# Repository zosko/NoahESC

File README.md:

# NoahESC
The Atmega8-based Electronic Speed Controller (ESC) is a motor control device that uses the Atmega8 microcontroller as its main processing unit. It is designed to regulate the speed, direction, and braking of brushless DC (BLDC) motors or brushed motors, depending on the application. The Atmega8 handles the input signals—typically from a flight controller or receiver—and converts them into precise pulse-width modulation (PWM) outputs to control the motor’s performance. This type of ESC is widely used in drones, RC vehicles, and robotics projects due to its reliability, programmability, and compatibility with open-source firmware such as TGY. Overall, it provides an efficient and flexible solution for motor speed control in embedded and hobbyist applications.

### Features
- [X] PWM
- [X] 30Amps
- [X] 2 - 4S battery
- [X] Low cost

## Scheme

## Boards Preview
Board|PCB
---------|---------
|

### Flashing
Atmega8 must be flashed via ICSP microcontroller pins. 

**Arduino UNO as ISP programmer**
- `avrdude -c stk500v1 -p m8 -P /dev/tty.usbmodem14401 -b 19200 -U flash:w:firmware.hex:i`
- `avrdude -c stk500v1 -p m8 -P /dev/tty.usbmodem14401 -b 19200 -U lfuse:w:0x3f:m -U hfuse:w:0xca:m`

**USBasp**
- `avrdude -c usbasp -p m8 -U flash:w:firmware.hex:i`
- `avrdude -c usbasp -p m8 -U lfuse:w:0x3f:m -U hfuse:w:0xca:m`

**Download**: [Firmware](firmware.hex)

## PCB Design

**Huge thanks to [PCBWay](https://pcbway.com) for sponsoring this project!**

PCBWay is a leading provider of high-quality printed circuit boards (PCBs), offering reliable and affordable solutions for both hobbyists and professionals. Their services include rapid prototyping, PCB assembly, instant online quotations, expert design verification, and a streamlined ordering experience.

Their comprehensive range of services includes:
- PCB prototyping
- Assembly services
- Instant online quotations
- Expert design verification
- A streamlined, user-friendly ordering system

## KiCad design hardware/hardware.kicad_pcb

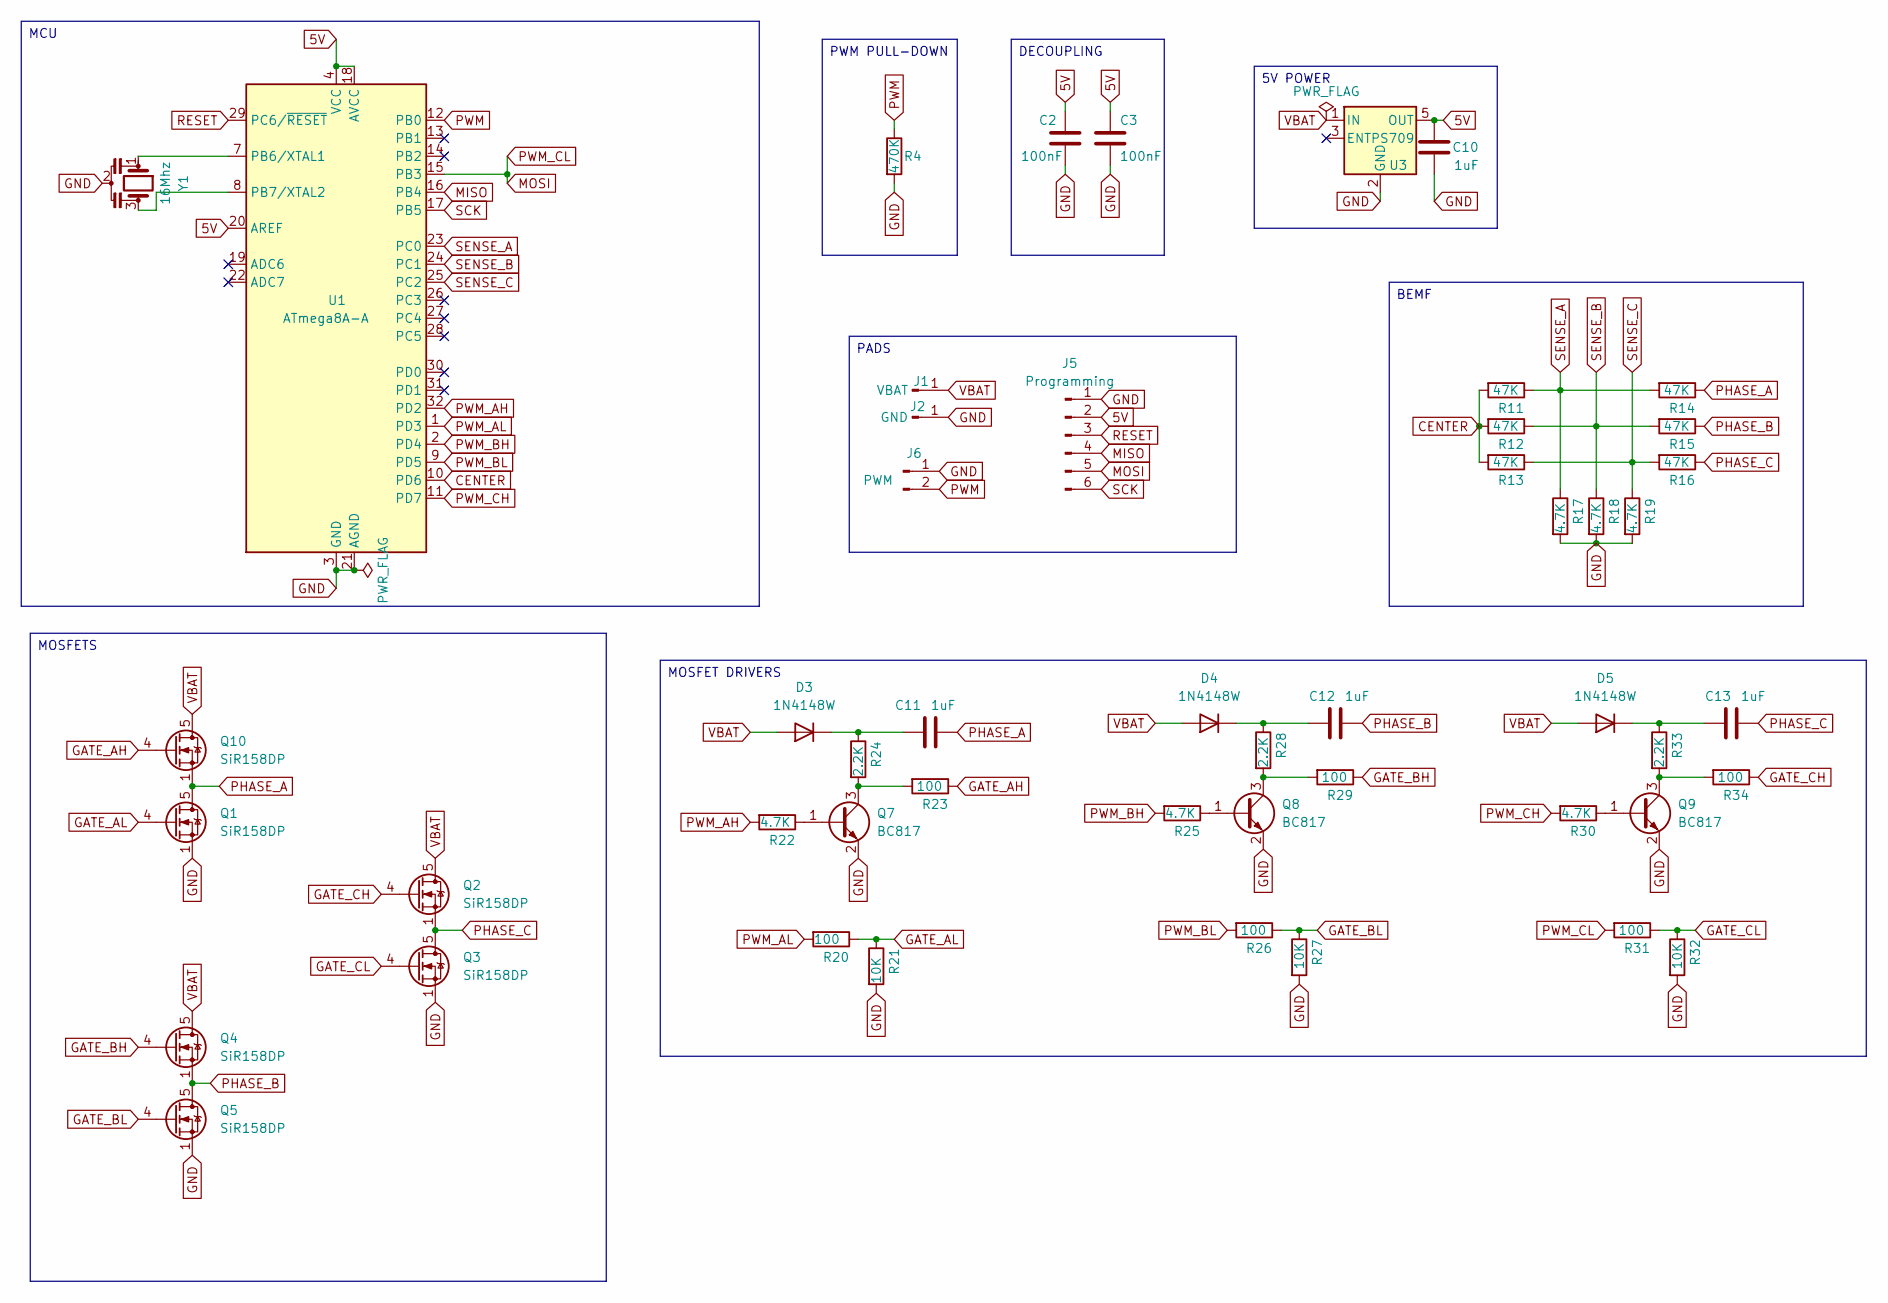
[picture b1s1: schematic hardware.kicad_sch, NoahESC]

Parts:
C2, C3: 100nF; C_0805_2012Metric_Pad1.18x1.45mm_HandSolder; LCSC C49678
C10, C11, C12, C13: 1uF; C_0805_2012Metric_Pad1.18x1.45mm_HandSolder; LCSC C28323
D3, D4, D5: 1N4148W; D_SOD-123; LCSC C241939
J1: VBAT; TestPoint_Pad_3.0x3.0mm
J2: GND; TestPoint_Pad_3.0x3.0mm
J5: Programming; PinHeader_1x06_P1.27mm_Vertical; LCSC C22438289
J6: PWM; PinHeader_1x02_P2.54mm_Vertical; LCSC C42431798
Q1, Q2, Q3, Q4, Q5, Q10: SiR158DP; PowerPAK_SO-8_Single; LCSC C142530
Q7, Q8, Q9: BC817; SOT-23; LCSC C39828
R4: 470K; R_0805_2012Metric_Pad1.20x1.40mm_HandSolder; LCSC C89104
R11, R12, R13, R14, R15, R16: 47K; R_0805_2012Metric_Pad1.20x1.40mm_HandSolder; LCSC C17713
R17, R18, R19, R22, R25, R30: 4.7K; R_0805_2012Metric_Pad1.20x1.40mm_HandSolder; LCSC C17673
R20, R23, R26, R29, R31, R34: 100; R_0805_2012Metric_Pad1.20x1.40mm_HandSolder; LCSC C17408
R21, R27, R32: 10K; R_0805_2012Metric_Pad1.20x1.40mm_HandSolder; LCSC C84376
R24, R28, R33: 2.2K; R_0805_2012Metric_Pad1.20x1.40mm_HandSolder; LCSC C17520
U1: ATmega8A-A; TQFP-32_7x7mm_P0.8mm; LCSC C16190
U3: TPS709; SOT-23-5; LCSC C2865456
Y1: 16Mhz; Resonator_SMD_Murata_CSTxExxV-3Pin_3.0x1.1mm; LCSC C882606

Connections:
5V: C2.1, C3.1, C10.2, J5.2, U1.4 (VCC), U1.6 (VCC), U1.18 (AVCC), U1.20 (AREF), U3.5 (OUT)
CENTER: R11.2, R12.2, R13.2, U1.10 (PD6)
GATE_AH: Q10.4 (G), R23.1
GATE_AL: Q1.4 (G), R20.1, R21.1
GATE_BH: Q4.4 (G), R29.1
GATE_BL: Q5.4 (G), R26.1, R27.1
GATE_CH: Q2.4 (G), R34.1
GATE_CL: Q3.4 (G), R31.1, R32.1
GND: C2.2, C3.2, C10.1, J2.1, J5.1, J6.1, Q1.1 (S), Q1.2 (S), Q1.3 (S), Q3.1 (S), Q3.2 (S), Q3.3 (S), Q5.1 (S), Q5.2 (S), Q5.3 (S), Q7.2 (E), Q8.2 (E), Q9.2 (E), R4.2, R17.2, R18.2, R19.2, R21.2, R27.2, R32.2, U1.3 (GND), U1.5 (GND), U1.21 (AGND), U3.2 (GND), Y1.2
MISO: J5.4, U1.16 (PB4)
MOSI: J5.5, R31.2, U1.15 (PB3)
unnamed: C11.2, D3.1 (K), R24.1
unnamed: C12.2, D4.1 (K), R28.1
unnamed: C13.2, D5.1 (K), R33.1
unnamed: Q7.1 (B), R22.1
unnamed: Q7.3 (C), R23.2, R24.2
unnamed: Q8.1 (B), R25.1
unnamed: Q8.3 (C), R28.2, R29.2
unnamed: Q9.1 (B), R30.1
unnamed: Q9.3 (C), R33.2, R34.2
unnamed: U1.7 (PB6/XTAL1), Y1.1
unnamed: U1.8 (PB7/XTAL2), Y1.3
PHASE_A: C11.1, Q1.5 (D), Q10.1 (S), Q10.2 (S), Q10.3 (S), R14.1
PHASE_B: C12.1, Q4.1 (S), Q4.2 (S), Q4.3 (S), Q5.5 (D), R15.1
PHASE_C: C13.1, Q2.1 (S), Q2.2 (S), Q2.3 (S), Q3.5 (D), R16.1
PWM: J6.2, R4.1, U1.12 (PB0)
PWM_AH: R22.2, U1.32 (PD2)
PWM_AL: R20.2, U1.1 (PD3)
PWM_BH: R25.2, U1.2 (PD4)
PWM_BL: R26.2, U1.9 (PD5)
PWM_CH: R30.2, U1.11 (PD7)
RESET: J5.3, U1.29 (PC6/~RESET)
SCK: J5.6, U1.17 (PB5)
SENSE_A: R11.1, R14.2, R17.1, U1.23 (PC0)
SENSE_B: R12.1, R15.2, R18.1, U1.24 (PC1)
SENSE_C: R13.1, R16.2, R19.1, U1.25 (PC2)
VBAT: D3.2 (A), D4.2 (A), D5.2 (A), J1.1, Q2.5 (D), Q4.5 (D), Q10.5 (D), U3.1 (IN)

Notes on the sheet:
MCU
BEMF
5V POWER
PADS
DECOUPLING
MOSFET DRIVERS
PWM PULL-DOWN
MOSFETS

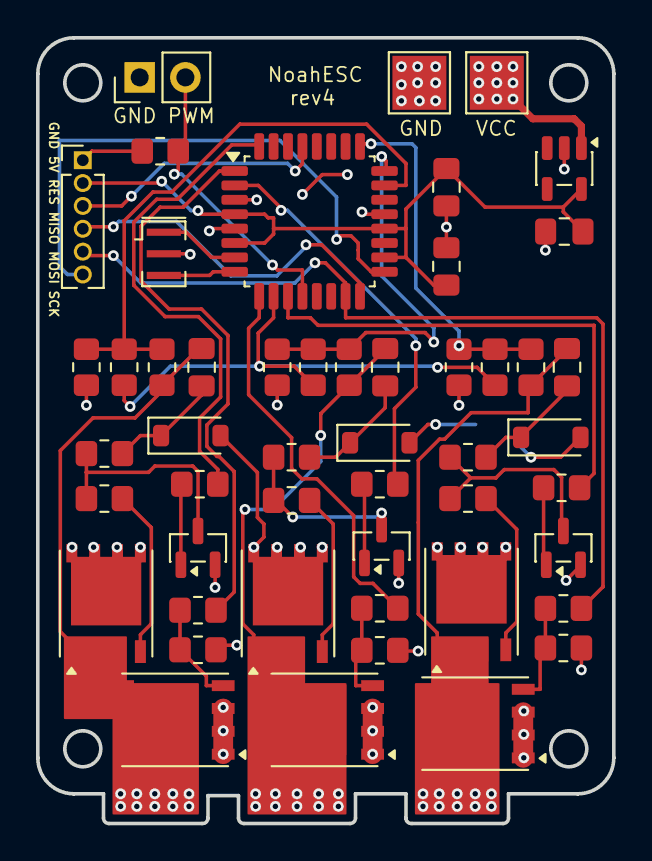
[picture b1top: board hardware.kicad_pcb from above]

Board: 2 copper layers, 32.0 x 43.7 mm, 50 parts (0 on the bottom side), 37 nets.

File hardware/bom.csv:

"Reference","Value","LCSC"
"C2,C3","100nF","C49678"
"C10,C11,C12,C13","1uF","C28323"
"D3,D4,D5","1N4148W","C241939"
"J1","VBAT",""
"J2,J3","GND",""
"J4","PWM",""
"J5","Programming","C22438289"
"Q1,Q2,Q3,Q4,Q5,Q10","SiR158DP","C142530"
"Q7,Q8,Q9","BC817","C39828"
"R4","470K","C89104"
"R11,R12,R13,R14,R15,R16","47K","C17713"
"R17,R18,R19,R22,R25,R30","4.7K","C17673"
"R20,R23,R26,R29,R31,R34","100","C17408"
"R21,R27,R32","10K","C84376"
"R24,R28,R33","2.2K","C17520"
"U1","ATmega8A-A","C16190"
"U3","TPS709","C2865456"
"Y1","16Mhz","C882606"

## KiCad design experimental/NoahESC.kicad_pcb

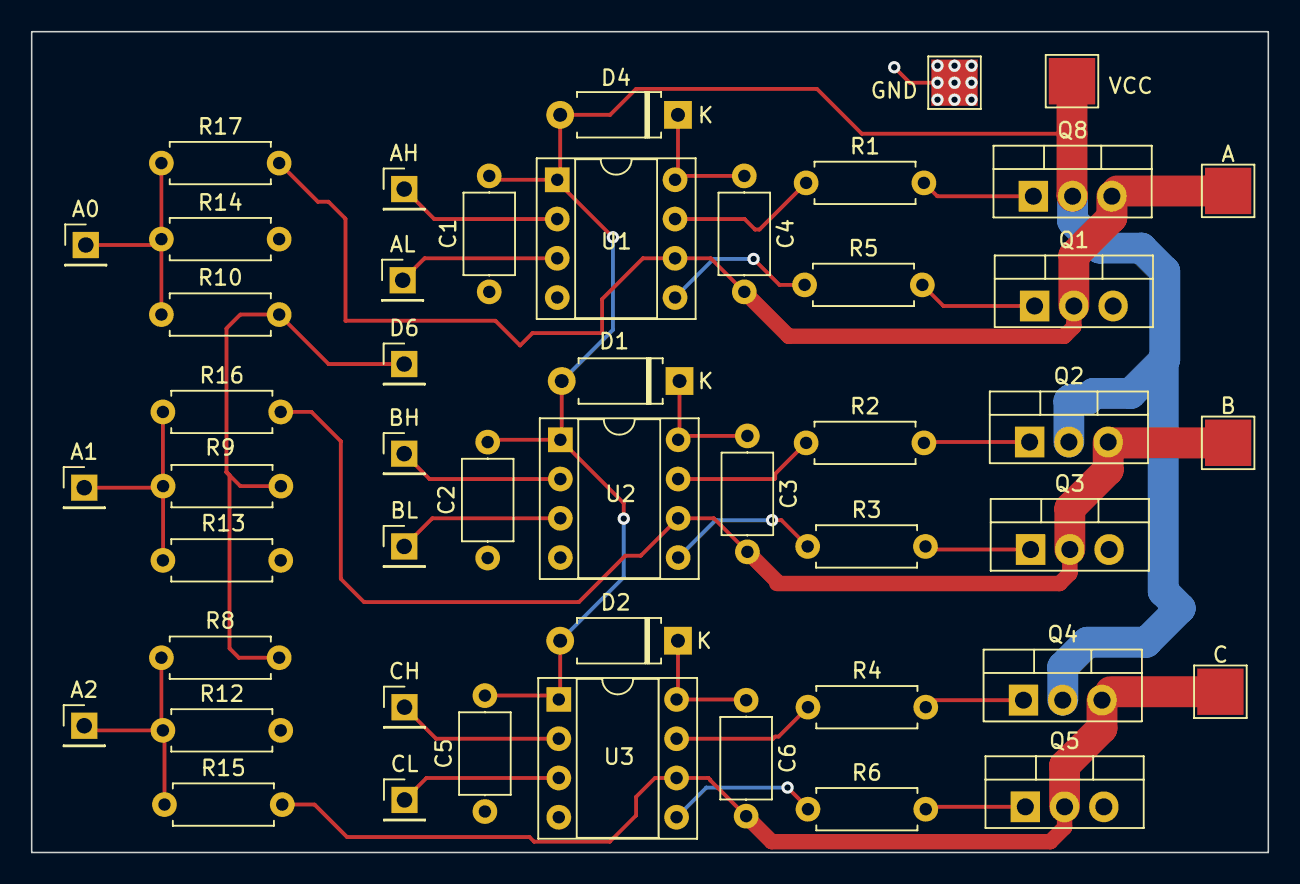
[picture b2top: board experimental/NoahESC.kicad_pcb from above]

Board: 2 copper layers, 80.0 x 53.1 mm, 48 parts (0 on the bottom side), 30 nets.

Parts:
A: PHASE_A; TestPoint_Pad_3.0x3.0mm
A0: A0; PinHeader_1x01_P2.54mm_Vertical
A1: A1; PinHeader_1x01_P2.54mm_Vertical
A2: A2; PinHeader_1x01_P2.54mm_Vertical
AH: AH; PinHeader_1x01_P2.54mm_Vertical
AL: AL; PinHeader_1x01_P2.54mm_Vertical
B: PHASE_B; TestPoint_Pad_3.0x3.0mm
BH: BH; PinHeader_1x01_P2.54mm_Vertical
BL: BL; PinHeader_1x01_P2.54mm_Vertical
C: PHASE_C; TestPoint_Pad_3.0x3.0mm
C1, C2, C5: 10uF; C_Axial_L5.1mm_D3.1mm_P7.50mm_Horizontal
C3, C4, C6: 2.2uF; C_Axial_L5.1mm_D3.1mm_P7.50mm_Horizontal
CH: CH; PinHeader_1x01_P2.54mm_Vertical
CL: CL; PinHeader_1x01_P2.54mm_Vertical
D1, D2, D4: D; D_A-405_P7.62mm_Horizontal
D6: D6; PinHeader_1x01_P2.54mm_Vertical
GND: GND; TestPoint_Pad_3.0x3.0mm
Q1, Q2, Q3, Q4, Q5, Q8: NMOS; TO-220-3_Vertical
R1, R2, R3, R4, R5, R6: 100; R_Axial_DIN0207_L6.3mm_D2.5mm_P7.62mm_Horizontal
R8, R9, R10, R15, R16, R17: 33K; R_Axial_DIN0207_L6.3mm_D2.5mm_P7.62mm_Horizontal
R12, R13, R14: 10K; R_Axial_DIN0207_L6.3mm_D2.5mm_P7.62mm_Horizontal
U1, U2, U3: IR2101; DIP-8_W7.62mm_Socket
VCC: 12V; TestPoint_Pad_3.0x3.0mm

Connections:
12V: C1.2, C2.2, C5.2, D1.2 (A), D2.2 (A), D4.2 (A), Q2.2 (D), Q4.2 (D), Q8.2 (D), U1.1 (VCC), U2.1 (VCC), U3.1 (VCC), VCC.1
A0: A0.1, R10.2, R14.1, R17.1
A1: A1.1, R9.2, R13.1, R16.1
A2: A2.1, R8.2, R12.1, R15.1
AH: AH.1, U1.2 (HIN)
AL: AL.1, U1.3 (LIN)
BH: BH.1, U2.2 (HIN)
BL: BL.1, U2.3 (LIN)
CH: CH.1, U3.2 (HIN)
CL: CL.1, U3.3 (LIN)
D6: D6.1, R8.1, R9.1, R10.1
GND: C1.1, C2.1, C5.1, GND.1, Q1.3 (S), Q3.3 (S), Q5.3 (S), R12.2, R13.2, R14.2, U1.4 (COM), U2.4 (COM), U3.4 (COM)
unnamed: C3.1, D1.1 (K), U2.8 (VB)
unnamed: C6.1, D2.1 (K), U3.8 (VB)
unnamed: C4.1, D4.1 (K), U1.8 (VB)
unnamed: Q1.1 (G), R5.2
unnamed: Q2.1 (G), R2.2
unnamed: Q3.1 (G), R3.2
unnamed: Q4.1 (G), R4.2
unnamed: Q5.1 (G), R6.2
unnamed: Q8.1 (G), R1.2
unnamed: R1.1, U1.7 (HO)
unnamed: R5.1, U1.5 (LO)
unnamed: R2.1, U2.7 (HO)
unnamed: R3.1, U2.5 (LO)
unnamed: R4.1, U3.7 (HO)
unnamed: R6.1, U3.5 (LO)
PHASE_A: A.1, C4.2, Q1.2 (D), Q8.3 (S), R17.2, U1.6 (VS)
PHASE_B: B.1, C3.2, Q2.3 (S), Q3.2 (D), R16.2, U2.6 (VS)
PHASE_C: C.1, C6.2, Q4.3 (S), Q5.2 (D), R15.2, U3.6 (VS)

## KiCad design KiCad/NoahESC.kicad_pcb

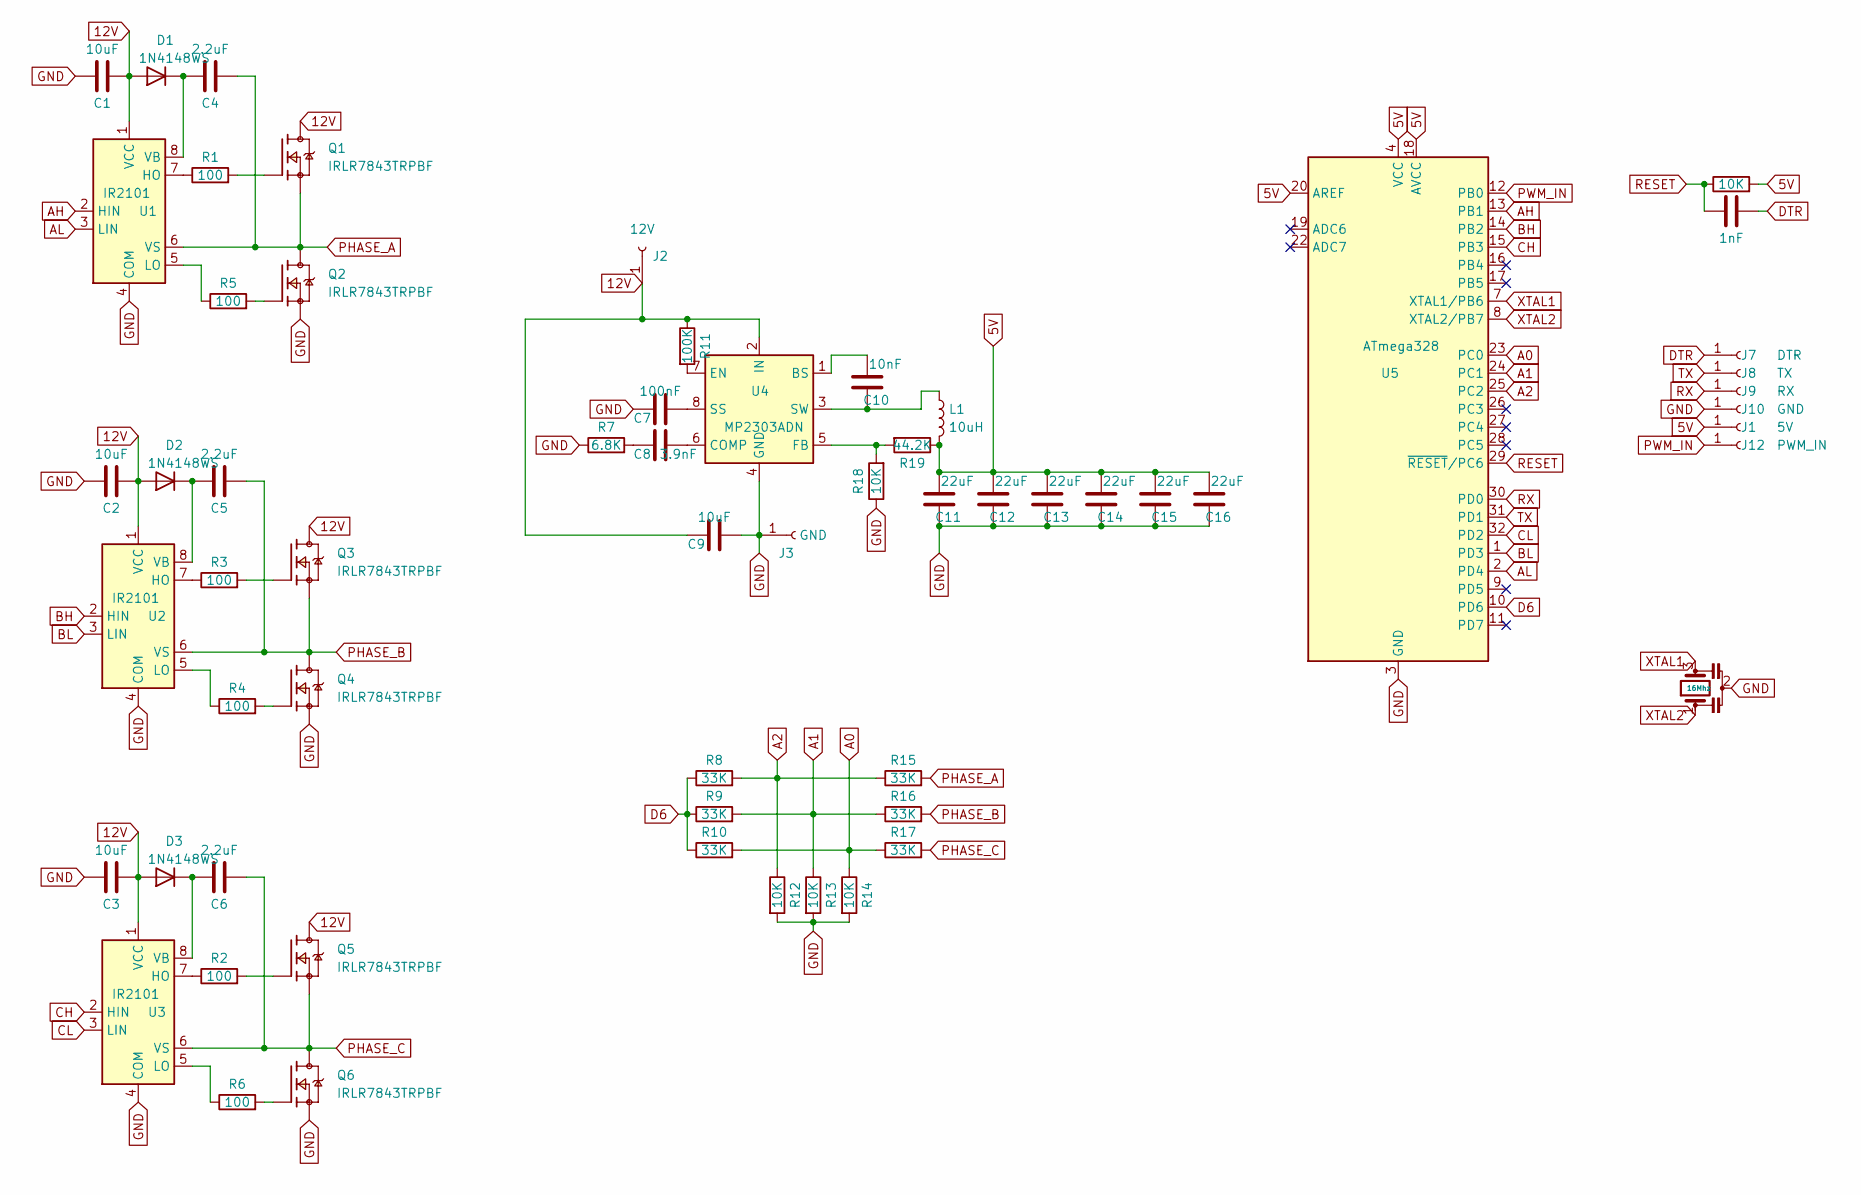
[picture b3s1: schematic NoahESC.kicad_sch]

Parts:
C1, C2, C3, C9: 10uF; C_0805_2012Metric
C4, C5, C6: 2.2uF; C_0805_2012Metric
C7: 100nF; C_0805_2012Metric
C8: 3.9nF; C_0805_2012Metric
C10: 10nF; C_0805_2012Metric
C11, C12, C13, C14, C15, C16: 22uF; C_0805_2012Metric
C17: 1nF; C_0805_2012Metric
D1, D2, D3: 1N4148WS; D_SOD-323
J1: 5V; SolderWirePad_1x01_SMD_1x2mm
J2: 12V; TestPoint_Pad_3.0x3.0mm
J3: GND; TestPoint_Pad_3.0x3.0mm
J7: DTR; SolderWirePad_1x01_SMD_1x2mm
J8: TX; SolderWirePad_1x01_SMD_1x2mm
J9: RX; SolderWirePad_1x01_SMD_1x2mm
J10: GND; SolderWirePad_1x01_SMD_1x2mm
J12: PWM_IN; SolderWirePad_1x01_SMD_1x2mm
L1: 10uH; L_7.3x7.3_H3.5
Q1, Q2, Q3, Q4, Q5, Q6: IRLR7843TRPBF; TO229P990X239-3_4N; PARTREV 04/30/08
R1, R2, R3, R4, R5, R6: 100; R_0805_2012Metric
R7: 6.8K; R_0805_2012Metric
R8, R9, R10, R15, R16, R17: 33K; R_0805_2012Metric
R11: 100K; R_0805_2012Metric
R12, R13, R14, R18, R20: 10K; R_0805_2012Metric
R19: 44.2K; R_0805_2012Metric
U1, U2, U3: IR2101; SOIC-8_3.9x4.9mm_P1.27mm
U4: MP2303ADN; SOIC-8_3.9x4.9mm_P1.27mm
U5: ATmega328; TQFP-32_7x7mm_P0.8mm
Y1: 16Mhz; Resonator_SMD_Murata_CSTxExxV-3Pin_3.0x1.1mm

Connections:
5V: C11.2, C12.2, C13.2, C14.2, C15.2, C16.2, J1.1, L1.2, R19.1, R20.2, U5.4 (VCC), U5.6 (VCC), U5.18 (AVCC), U5.20 (AREF)
12V: C1.2, C2.2, C3.2, C9.1, D1.2 (A), D2.2 (A), D3.2 (A), J2.1, Q1.4, Q3.4, Q5.4, R11.1, U1.1 (VCC), U2.1 (VCC), U3.1 (VCC), U4.2 (IN)
A0: R10.2, R14.1, R17.1, U5.23 (PC0)
A1: R9.2, R13.1, R16.1, U5.24 (PC1)
A2: R8.2, R12.1, R15.1, U5.25 (PC2)
AH: U1.2 (HIN), U5.13 (PB1)
AL: U1.3 (LIN), U5.2 (PD4)
BH: U2.2 (HIN), U5.14 (PB2)
BL: U2.3 (LIN), U5.1 (PD3)
CH: U3.2 (HIN), U5.15 (PB3)
CL: U3.3 (LIN), U5.32 (PD2)
D6: R8.1, R9.1, R10.1, U5.10 (PD6)
DTR: C17.2, J7.1
GND: C1.1, C2.1, C3.1, C7.1, C9.2, C11.1, C12.1, C13.1, C14.1, C15.1, C16.1, J3.1, J10.1, Q2.3, Q4.3, Q6.3, R7.1, R12.2, R13.2, R14.2, R18.1, U1.4 (COM), U2.4 (COM), U3.4 (COM), U4.4 (GND), U5.3 (GND), U5.5 (GND), U5.21 (GND), Y1.2
unnamed: C4.1, D1.1 (K), U1.8 (VB)
unnamed: C5.1, D2.1 (K), U2.8 (VB)
unnamed: C6.1, D3.1 (K), U3.8 (VB)
unnamed: C7.2, U4.8 (SS)
unnamed: C8.1, R7.2
unnamed: C8.2, U4.6 (COMP)
unnamed: C10.1, L1.1, U4.3 (SW)
unnamed: C10.2, U4.1 (BS)
unnamed: Q1.1, R1.2
unnamed: Q2.1, R5.2
unnamed: Q3.1, R3.2
unnamed: Q4.1, R4.2
unnamed: Q5.1, R2.2
unnamed: Q6.1, R6.2
unnamed: R1.1, U1.7 (HO)
unnamed: R2.1, U3.7 (HO)
unnamed: R3.1, U2.7 (HO)
unnamed: R4.1, U2.5 (LO)
unnamed: R5.1, U1.5 (LO)
unnamed: R6.1, U3.5 (LO)
unnamed: R11.2, U4.7 (EN)
unnamed: R18.2, R19.2, U4.5 (FB)
PHASE_A: C4.2, Q1.3, Q2.4, R15.2, U1.6 (VS)
PHASE_B: C5.2, Q3.3, Q4.4, R16.2, U2.6 (VS)
PHASE_C: C6.2, Q5.3, Q6.4, R17.2, U3.6 (VS)
PWM_IN: J12.1, U5.12 (PB0)
RESET: C17.1, R20.1, U5.29 (~RESET/PC6)
RX: J9.1, U5.30 (PD0)
TX: J8.1, U5.31 (PD1)
XTAL1: U5.7 (XTAL1/PB6), Y1.3
XTAL2: U5.8 (XTAL2/PB7), Y1.1

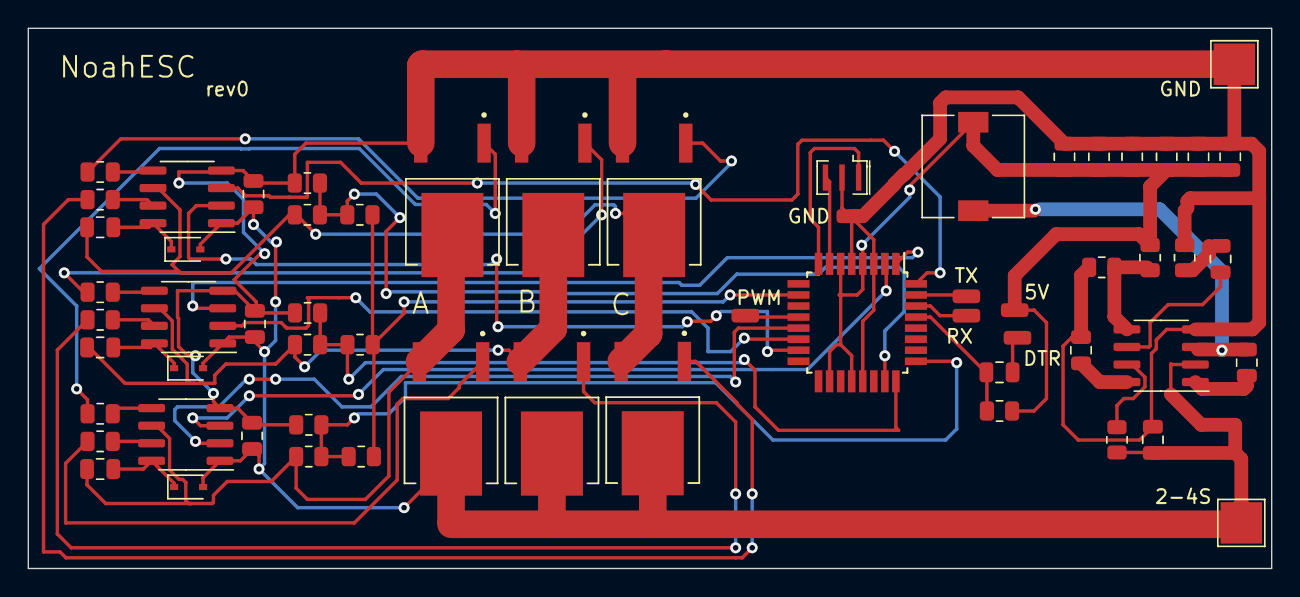
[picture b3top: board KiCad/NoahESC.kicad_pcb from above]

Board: 2 copper layers, 90.0 x 39.1 mm, 61 parts (0 on the bottom side), 45 nets.

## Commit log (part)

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2022-08-02 update doc
2022-08-02 fix pcb
2022-08-02 refactor firmware
2022-08-03 improve
2022-08-03 refactor code
2022-10-01 rename folder
2022-12-23 experimental version
2023-06-27 DIP version
2023-11-30 remove experimental
2023-11-30 remove firmware
2023-11-30 update project to rev1
2023-11-30 update images
2023-11-30 add scheme
2023-11-30 additional vcc / gnd
2024-02-28 update to kicad 8
2024-03-04 add rev1 board - single side
2024-03-04 pdf scheme rev1
2024-03-04 add images for rev1
2024-03-12 add test firmware
2024-04-16 add rev2
2024-04-20 add solder mask on bottom plate
2024-04-20 unused 3d model
2024-07-02 rename capacitors
2025-07-31 remove pdf scheme
2025-07-31 add new images
2025-07-31 update rev3 board
2025-12-01 add bom file
2025-12-01 add rev4
2025-12-04 add new pwm pin
2025-12-21 added pick and place
